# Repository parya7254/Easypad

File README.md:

# Easypad
A macropad which has switchable modes! It will contain various shortcuts to make using a computer easier (such as ctrl+c, ctrl+v, etc.). It uses a 4x4 button matrix, Neopixel LEDs, and a 0.91" 128x32 SSD1306 Monochrome OLED Display

# BOM:
- 1x Seeed XIAO RP2040
- 1x 0.91 inch OLED display
- 16x Cherry MX switches
- 1x PCB
- 16x Through-hole 1N4148 Diodes
- 16x SK6812 MINI-E LEDs
- 4x M3x16mm screws
- 4x M3x5mx4mm heatset inserts

# PCB and Schematic

# Case

# My Experiance:
While making my macropad, I really learned a lot about using Fusion to make 3D models and also using KiCad to make my first PCB! I had a lot of fun and really enjoyed the experience of doing what I have always wanted to do. Thank you Hack Club for giving me the helpful tutorials and resources to make my first macropad!

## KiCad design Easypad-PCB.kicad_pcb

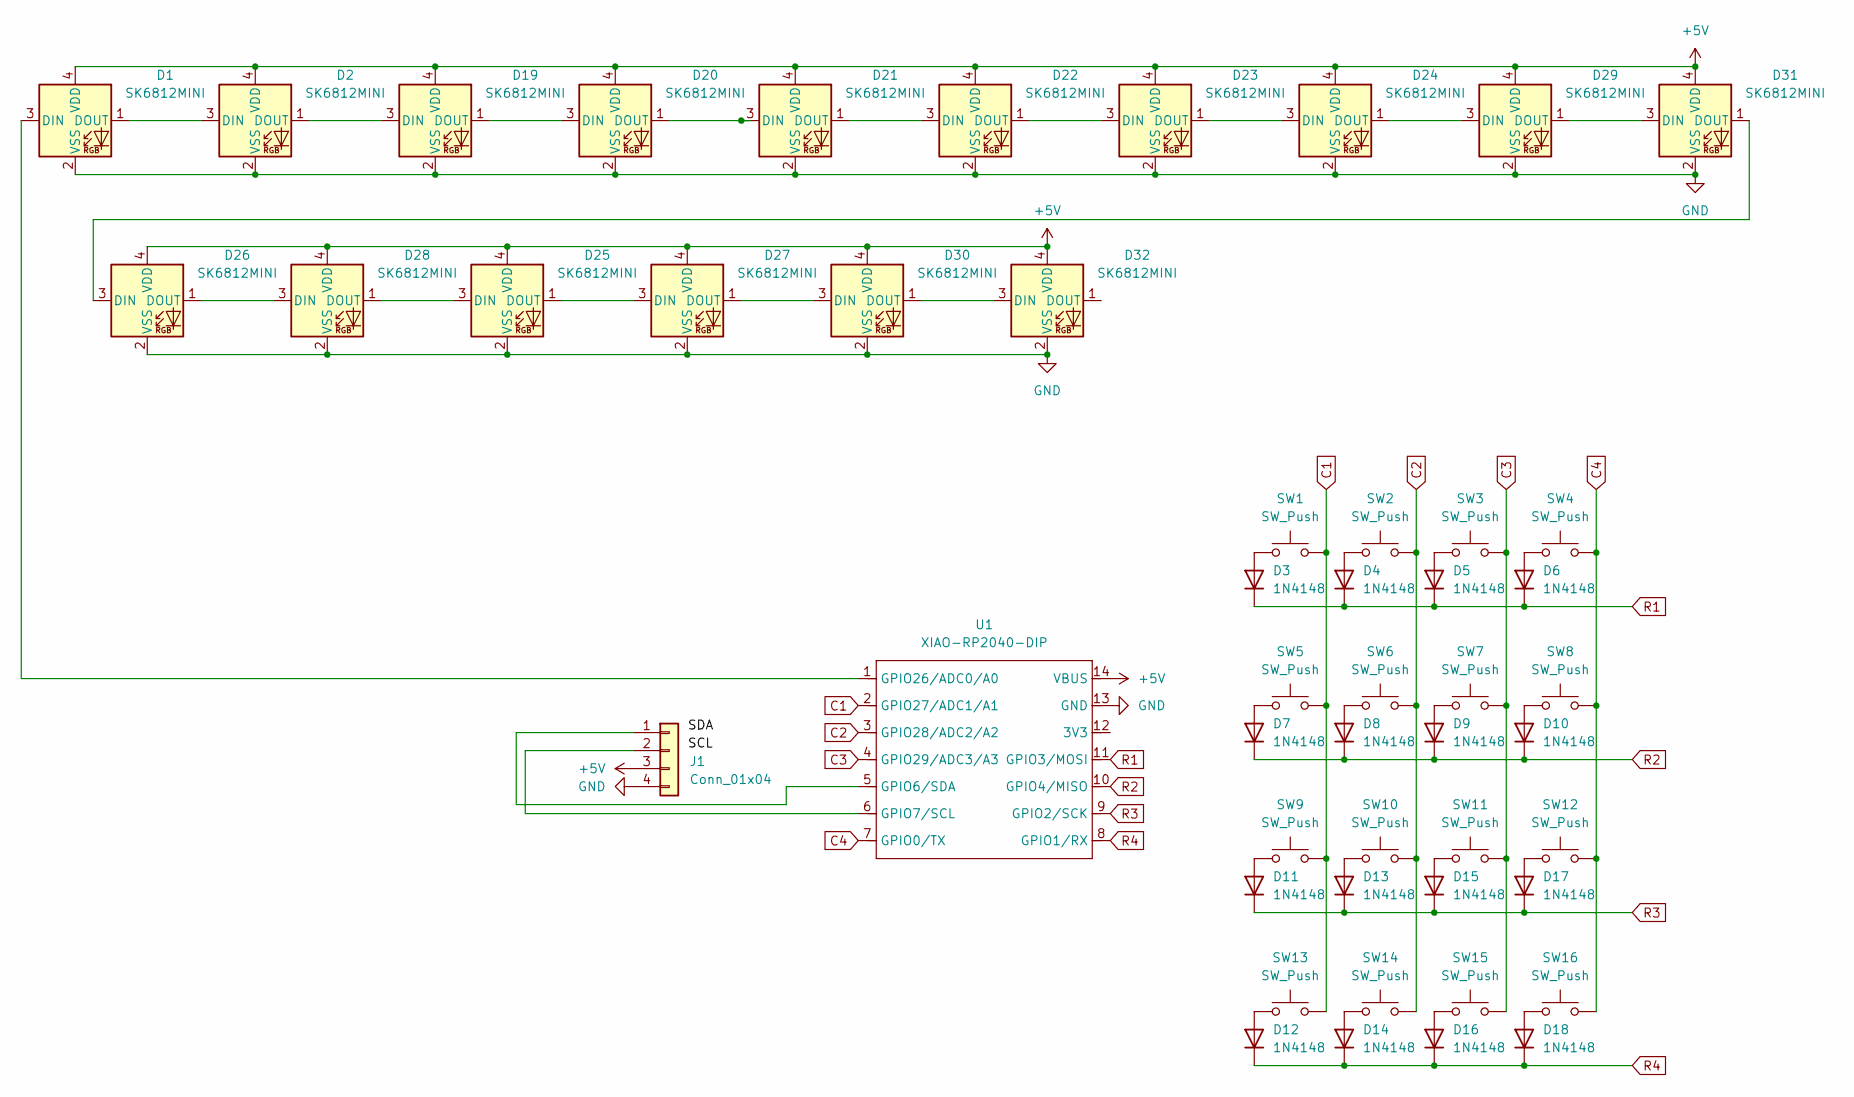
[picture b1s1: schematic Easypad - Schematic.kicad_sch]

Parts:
D1, D2, D19, D20, D21, D22, D23, D24, D25, D26, D27, D28, D29, D30, D31, D32: SK6812MINI; LED_SK6812MINI_PLCC4_3.5x3.5mm_P1.75mm
D3, D4, D5, D6, D7, D8, D9, D10, D11, D12, D13, D14, D15, D16, D17, D18: 1N4148; D_DO-35_SOD27_P7.62mm_Horizontal
J1: Conn_01x04; PinHeader_1x04_P2.54mm_Vertical
SW1, SW2, SW3, SW4, SW5, SW6, SW7, SW8, SW9, SW10, SW11, SW12, SW13, SW14, SW15, SW16: SW_Push; SW_Cherry_MX_1.00u_PCB
U1: XIAO-RP2040-DIP

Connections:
+5V: D1.4 (VDD), D2.4 (VDD), D19.4 (VDD), D20.4 (VDD), D21.4 (VDD), D22.4 (VDD), D23.4 (VDD), D24.4 (VDD), D25.4 (VDD), D26.4 (VDD), D27.4 (VDD), D28.4 (VDD), D29.4 (VDD), D30.4 (VDD), D31.4 (VDD), D32.4 (VDD), J1.3, U1.14 (VBUS)
C1: SW1.2, SW5.2, SW9.2, SW13.2, U1.2 (GPIO27/ADC1/A1)
C2: SW2.2, SW6.2, SW10.2, SW14.2, U1.3 (GPIO28/ADC2/A2)
C3: SW3.2, SW7.2, SW11.2, SW15.2, U1.4 (GPIO29/ADC3/A3)
C4: SW4.2, SW8.2, SW12.2, SW16.2, U1.7 (GPIO0/TX)
GND: D1.2 (VSS), D2.2 (VSS), D19.2 (VSS), D20.2 (VSS), D21.2 (VSS), D22.2 (VSS), D23.2 (VSS), D24.2 (VSS), D25.2 (VSS), D26.2 (VSS), D27.2 (VSS), D28.2 (VSS), D29.2 (VSS), D30.2 (VSS), D31.2 (VSS), D32.2 (VSS), J1.4, U1.13 (GND)
unnamed: D1.3 (DIN), U1.1 (GPIO26/ADC0/A0)
unnamed: D1.1 (DOUT), D2.3 (DIN)
unnamed: D3.2 (A), SW1.1
unnamed: D4.2 (A), SW2.1
unnamed: D5.2 (A), SW3.1
unnamed: D6.2 (A), SW4.1
unnamed: D7.2 (A), SW5.1
unnamed: D8.2 (A), SW6.1
unnamed: D9.2 (A), SW7.1
unnamed: D10.2 (A), SW8.1
unnamed: D11.2 (A), SW9.1
unnamed: D12.2 (A), SW13.1
unnamed: D13.2 (A), SW10.1
unnamed: D14.2 (A), SW14.1
unnamed: D15.2 (A), SW11.1
unnamed: D16.2 (A), SW15.1
unnamed: D17.2 (A), SW12.1
unnamed: D18.2 (A), SW16.1
unnamed: D2.1 (DOUT), D19.3 (DIN)
unnamed: D19.1 (DOUT), D20.3 (DIN)
unnamed: D20.1 (DOUT), D21.3 (DIN)
unnamed: D21.1 (DOUT), D22.3 (DIN)
unnamed: D22.1 (DOUT), D23.3 (DIN)
unnamed: D23.1 (DOUT), D24.3 (DIN)
unnamed: D24.1 (DOUT), D29.3 (DIN)
unnamed: D25.3 (DIN), D28.1 (DOUT)
unnamed: D25.1 (DOUT), D27.3 (DIN)
unnamed: D26.3 (DIN), D31.1 (DOUT)
unnamed: D26.1 (DOUT), D28.3 (DIN)
unnamed: D27.1 (DOUT), D30.3 (DIN)
unnamed: D29.1 (DOUT), D31.3 (DIN)
unnamed: D30.1 (DOUT), D32.3 (DIN)
unnamed: J1.1, U1.5 (GPIO6/SDA)
unnamed: J1.2, U1.6 (GPIO7/SCL)
R1: D3.1 (K), D4.1 (K), D5.1 (K), D6.1 (K), U1.11 (GPIO3/MOSI)
R2: D7.1 (K), D8.1 (K), D9.1 (K), D10.1 (K), U1.10 (GPIO4/MISO)
R3: D11.1 (K), D13.1 (K), D15.1 (K), D17.1 (K), U1.9 (GPIO2/SCK)
R4: D12.1 (K), D14.1 (K), D16.1 (K), D18.1 (K), U1.8 (GPIO1/RX)

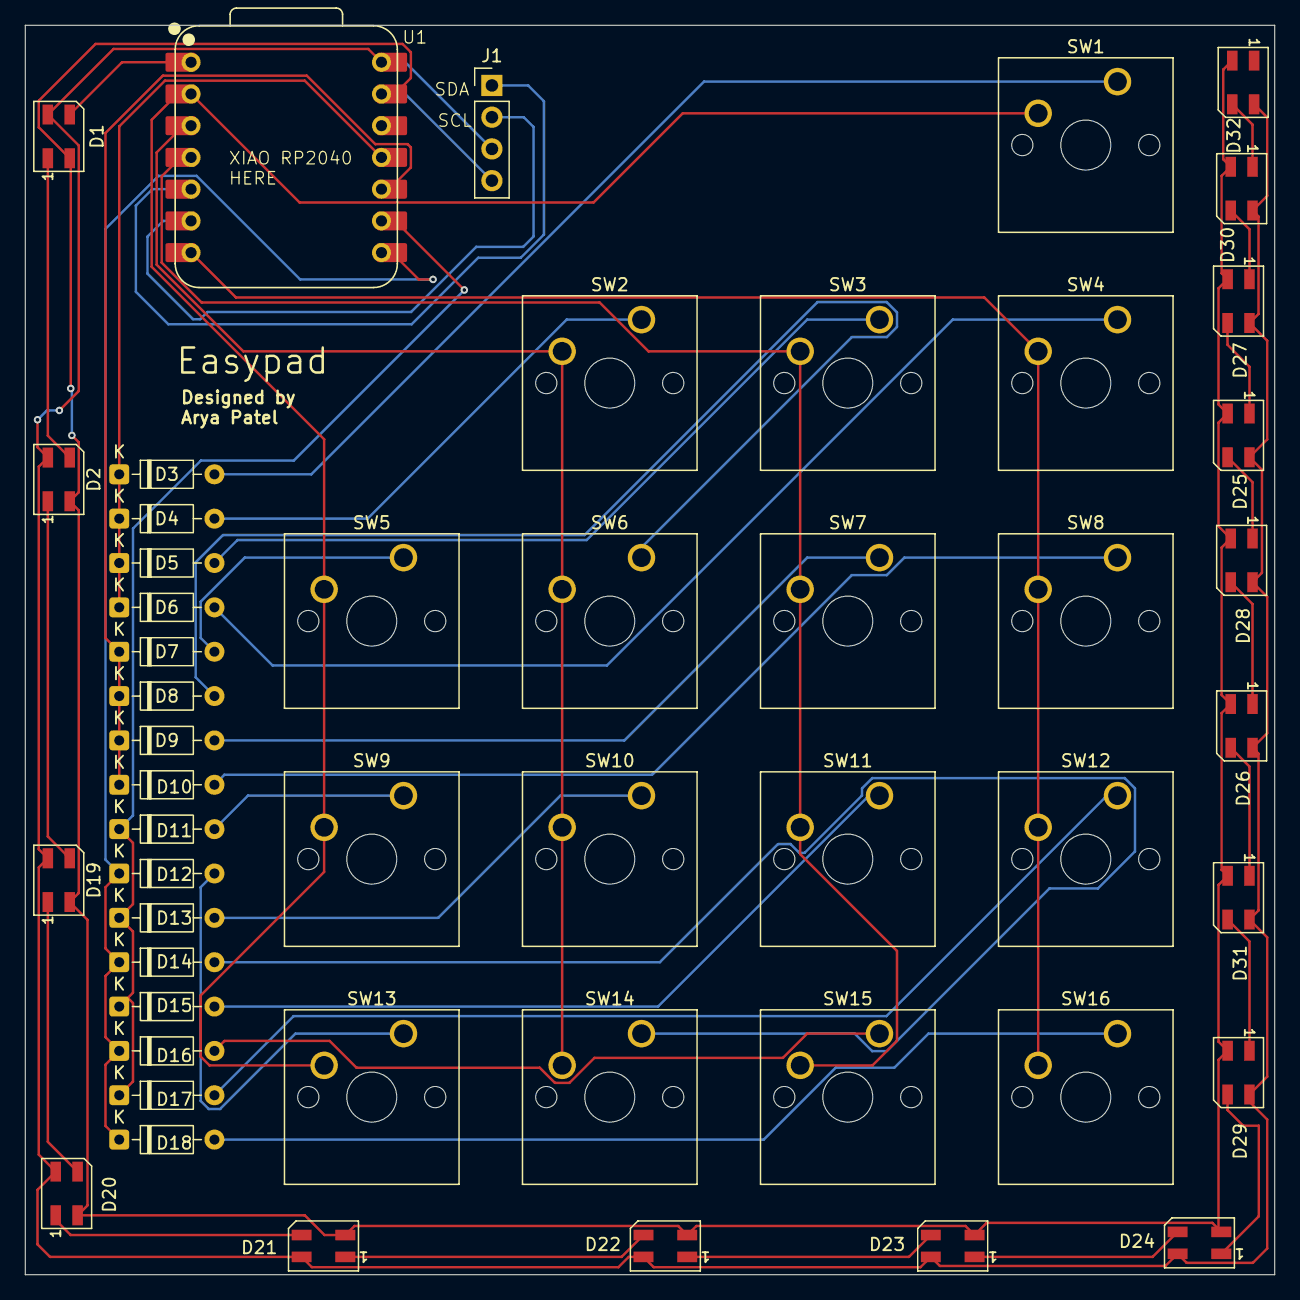
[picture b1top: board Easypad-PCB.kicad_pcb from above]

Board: 2 copper layers, 100.0 x 100.0 mm, 50 parts (0 on the bottom side), 44 nets.

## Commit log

2026-01-05 Create cad
2026-01-24 Create file
2026-01-24 Add Easypad - Assembled.step
2026-01-24 Delete CAD/Easypad - Assembled.step
    Wrong file, not the updated version
2026-01-24 Create pcb
2026-01-24 Enhance README with BOM and project details
    Added detailed sections including BOM, PCB and schematic images, case image, and personal experience.
2026-05-27 Enhance README with images and project description
    Added images and updated description for Easypad.
